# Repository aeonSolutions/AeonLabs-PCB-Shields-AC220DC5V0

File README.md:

# AeonLabs PCB Shields AC 85V-220V to DC 5.0V
 This is a pcb design for a AC220V 1A to DC 5V0 converter. With 220V fuse for increased safety. Suitable as a add-on design for any other KiCad project.

*Don't forget to LIKE , SHARE and subscribe the free whatsApp group* and if you liked this PCB consider buying me a cup of coffee. Links below.

### Status
  revision 1.1 fully tested and working.

If you already tested this PCB send me a message. Thank you

## Revisions
- revision 1.1 
  - bug track corrections
  - added overcurrent protection 
 
## Download options
Download this repository if you need the KiCad Files or, download the Gerber files in the release section of this repository

## Liked it ? Get a Free PCB for yourself
Send me your Device or hardware and i will design a custom PCB for it. Free of charge. Contact-me on WhatsApp or email for more info. 

## Q&A WhatsApp Group
If you have any Questions or simply  like this kind of projects and want to stay updated with the latest research ideas and prototypes during the day and week, join the WhatsApp Group
[A.I. Things](https://chat.whatsapp.com/FkNC7u83kuy2QRA5sqjBVg)

## Fully assembled PCB
Alternatively, and if you do not want to build a PCB by yourself and like to buy one, you can do it here:

The price will be around 30eur plus postage fees.
(I will also deliver the assembled PCB with all the components in place at a fair aditonal cost).

This PCB is a #direct fit #replacement of the one found on the internet at sale. For example here: https://s.click.aliexpress.com/e/_9wRPxz

#### Be supportive of my dedication and work towards technology education and buy me a coffee. Link below.

view me testing this pcb module with a multimeter on youtube, [here](https://youtu.be/aK8yDyUbOkI)

________________________________________________________________________________________________________________

## PCB Parts list
- [Capacitor 2.2uF SMD](https://s.click.aliexpress.com/e/_AVdmzr)
- [Resistor SMD ](https://s.click.aliexpress.com/e/_A7OXrR)
- [EE10-A1 switching power supply transformer 220V to 5-12V](https://s.click.aliexpress.com/e/_DDHkwsf)
- [4.7uF 400V Electrolitic Capacitor](https://s.click.aliexpress.com/e/_DlkOyWT)
- [390uF 6.3V Solid Electrolitic Capacitor](https://s.click.aliexpress.com/e/_DkZ4zmf)
- [SS36 rectifier Diode](https://s.click.aliexpress.com/e/_DFlMjfv)
- [MB10F 4 Diode Bridge Rectifier](https://s.click.aliexpress.com/e/_DcfTow3)
- [HT2812H AC DC 5W charging](https://s.click.aliexpress.com/e/_Dk6dCGB)

## Firmware Download 
one can use the PCB in the repository [AeonLabs-MCU-Burner-USB-to-UART-TTL](https://github.com/aeonSolutions/AeonLabs-MCU-Burner-USB-to-UART-TTL) to program the ESP32 WROOM32 MCU on this PCB.

______________________________________________________________________________________________________________________________

### License
2022 Creative Commons Attribution-NonCommercial-ShareAlike 4.0 International

https://creativecommons.org/licenses/by-nc-sa/4.0/

### Own a copy of this work
if you like to own a copy of this work, you can buy it as a NFT or Ethereum. contact me for more details at mtpsilva@gmail.com
________________________________________________________________________________________________________________
## [Go back to main catalogue page](https://github.com/aeonSolutions/PCB-Prototyping-Catalogue)
________________________________________________________________________________________________________________

### Share this PCB board files

### Be supportive of my dedication and work towards technology education and buy me a coffee

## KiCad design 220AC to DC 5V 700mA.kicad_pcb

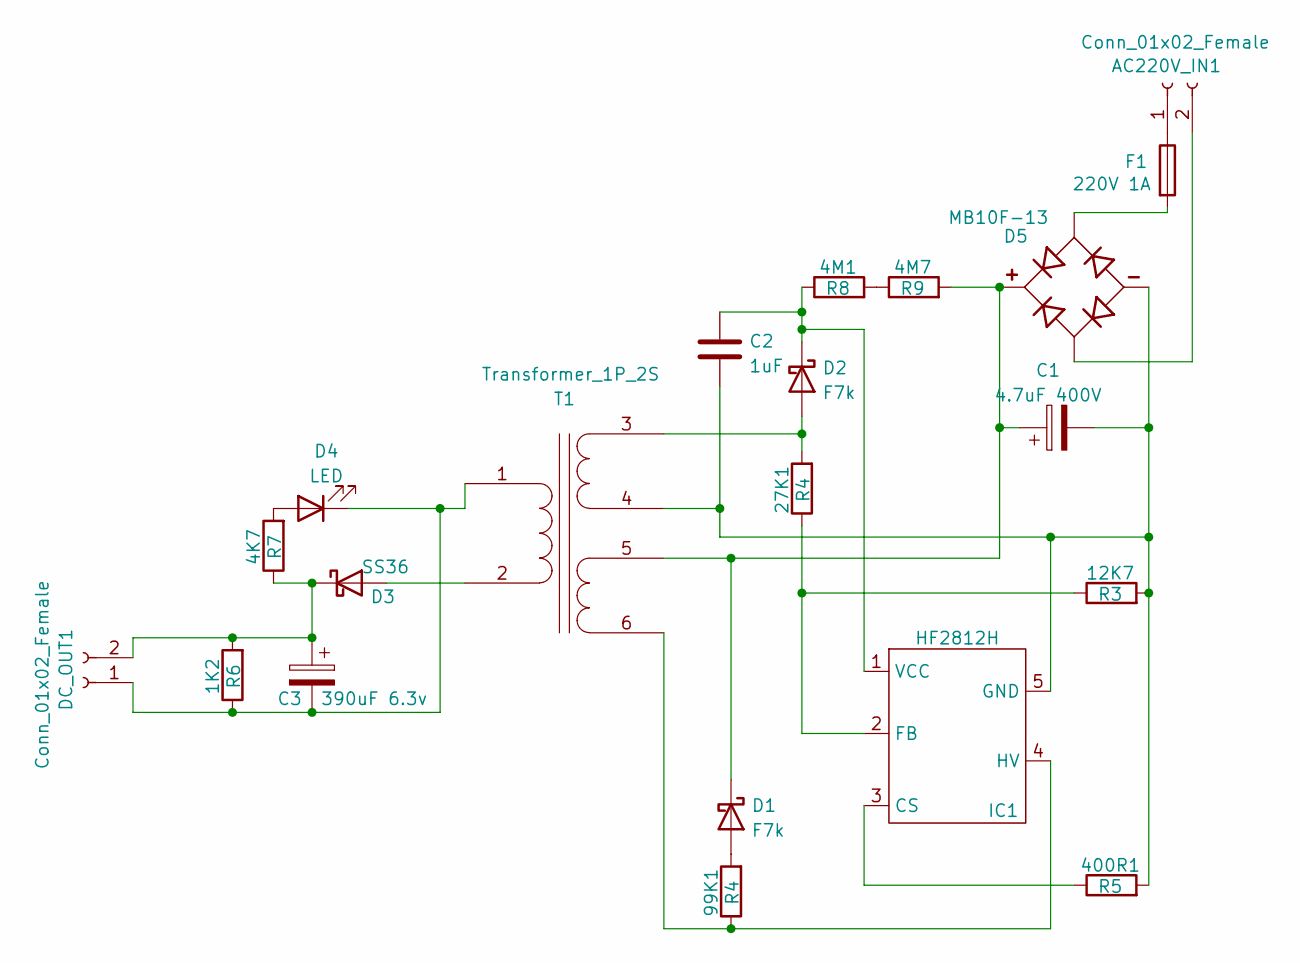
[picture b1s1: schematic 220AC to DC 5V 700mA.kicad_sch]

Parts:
1K2: R6; R_0805_2012Metric_Pad1.20x1.40mm_HandSolder
4K7: R7; R_0805_2012Metric_Pad1.20x1.40mm_HandSolder
4M1: R8; R_0805_2012Metric_Pad1.20x1.40mm_HandSolder
4M7: R9; R_0805_2012Metric_Pad1.20x1.40mm_HandSolder
12K7: R3; R_0805_2012Metric_Pad1.20x1.40mm_HandSolder
27K1, 99K1: R4; R_0805_2012Metric_Pad1.20x1.40mm_HandSolder
400R1: R5; R_0805_2012Metric_Pad1.20x1.40mm_HandSolder
AC220V_IN1: Conn_01x02_Female; TestPoint_Pad_D1.5mm x2
C1: 4.7uF 400V; CP_Radial_D5.0mm_P2.00mm
C2: 1uF; C_0805_2012Metric_Pad1.18x1.45mm_HandSolder
C3: 390uF 6.3v; CP_Radial_D4.0mm_P1.50mm
D1, D2: F7k; D_1206_3216Metric_Pad1.42x1.75mm_HandSolder
D3: SS36; D_1206_3216Metric_Pad1.42x1.75mm_HandSolder
D4: LED; D_0805_2012Metric_Pad1.15x1.40mm_HandSolder
D5: MB10F-13; DIOB_MB10F-13; PARTREV 3 - 2
DC_OUT1: Conn_01x02_Female; TestPoint_Pad_D1.0mm x2
F1: 220V 1A; Fuse_Bourns_MF-RG300
IC1: HF2812H; SOP5
T1: Transformer_1P_2S; Transformer_EE10-A1 11.5x12.5mm

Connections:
unnamed: 1K2.1, C3.2, D4.1 (K), DC_OUT1.1, T1.1 (AA)
unnamed: 1K2.2, 4K7.1, C3.1, D3.1 (K), DC_OUT1.2
unnamed: 4K7.2, D4.2 (A)
unnamed: 4M1.1, C2.1, D2.1 (K), IC1.1 (VCC)
unnamed: 4M1.2, 4M7.1
unnamed: 4M7.2, C1.1, D1.1 (K), D5.1, T1.5 (SC)
unnamed: 12K7.1, 27K1.1, IC1.2 (FB)
unnamed: 12K7.2, 400R1.2, C1.2, C2.2, D5.3, IC1.5 (GND), T1.4 (SB)
unnamed: 27K1.2, D2.2 (A), T1.3 (SA)
unnamed: 99K1.1, IC1.4 (HV), T1.6 (SD)
unnamed: 99K1.2, D1.2 (A)
unnamed: 400R1.1, IC1.3 (CS)
unnamed: AC220V_IN1.1, F1.1
unnamed: AC220V_IN1.2, D5.4
unnamed: D3.2 (A), T1.2 (AB)
unnamed: D5.2, F1.2

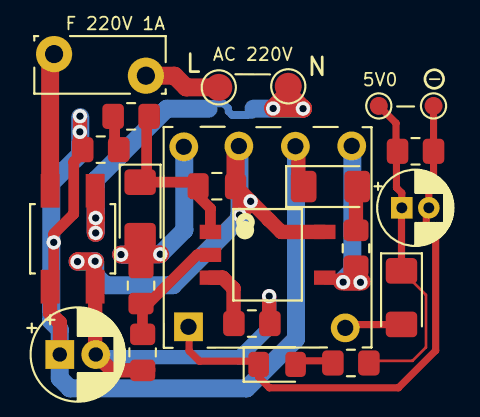
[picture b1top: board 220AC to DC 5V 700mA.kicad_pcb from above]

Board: 2 copper layers, 21 parts (0 on the bottom side), 16 nets.

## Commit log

2022-06-25 rev 1.0
2022-07-20 rev. update
    bug track correction ; added overcurrent protection
